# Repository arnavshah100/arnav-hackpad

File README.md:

# arnav-hackpad
<b>The arnav-hackpad is a mini-keyboard (or macropad) designed to act as an external number pad with navigation and mouse capabilities, too!</b>

## Inspiration
In my essential technology class at school, two of my favorite modules were coding and 3D printing. When I joined the [Stardance summer program](https://stardance.hackclub.com/) and started looking at the recommended projects, I saw <b>hackpad</b>, and saw it as a great way to combine my love for those two subjects.
## Features
- 2 EC11 Rotary Encoders with Switches
- 10 MX-Style Key Switches
- 3-Part Case (Top Mount style macropad)
- 2 Layers (When a layer is activated, all the keymaps change to that layer's configuration.)
## CAD Model
\
This is my assembled macropad. Click on it to interact with the assembled macropad in Autodesk Fusion's web version.\
_Note: The assembled macropad CAD model is just a quick visual. Some of the dimensions have been edited to optimize its usability. The links of the individual parts below have the correct dimensions._ 

There are 3 parts to the case: the top, the bottom, and the plate. The arnav-hackpad is top-mounted, meaning that the plate is attached to the top part. The design gives an ≈0.3mm printing tolerance. Also, there are 2 knobs I have put on top of the rotary encoders, called Hack Club Knurled Knobs. To personalize it, I added a cool design with my name on the plate, which you can see in the plate demo below!

[Click here to interact with the Plate.](https://a360.co/4g3hhWc)\
[Click here to interact with the Top part.](https://a360.co/4vbjJyh)\
[Click here to interact with the  Bottom part.](https://a360.co/4pMDXNC)\
[Click here to interact with the Hack Club Knurled Knob.](https://a360.co/4jsLTTg)
## PCB

This is my PCB's schematic design. Click on it to interact with the schematic in KiCanvas.

I used a PCF8574AT I/O expander because all of the pins would not fit on the microchip.

This is my PCB board. Click on it to interact with the PCB Board in KiCanvas.

I know it's very messy, but everything works out in the end!
## Firmware Overview
The macropad is coded using KMK firmware. Layer 0 is made to take the place of a number pad, and Layer 1 is made to take the place of a mouse and the arrow keys. For the rotary encoders, clockwise is up, and counterclockwise is down.
- On Layer 0 (Default),
    - The rotary encoder on the left changes volume, and its switch works as the mute key.
    - The rotary encoder on the right changes brightness, and its switch turns on layer 1.
    - The key switches are arranged in the same way as the numbers are in a number pad. 
- On Layer 1,
    - The rotary encoder on the left acts as a scroll wheel.
    - The rotary encoder on the right also acts as a scroll wheel, and its switch turns on layer 0.
    - The keyswitches are arranged as follows(refer to the PCB image):
        - SW1 is Left Click
        - SW2 is Up Arrow
        - SW3 is Right Click
        - SW4 is Left Arrow
        - SW5 is Down Arrow
        - SW6 is Right Arrow

_Note: All of the key arrangements can be customized by simply editing the code._
## How to make it
<b>If you need help for any part of this tutorial, Google can teach you!</b>
### Bill of Materials
To make this macropad, you will need the following:
- 10x Cherry MX Switches
- 10x 1N4148 DO-35 Diodes
- 10x DSA Keycaps
- 2x EC11 Rotary Encoder
- 2x Hack Club Knurled Knob (Replaceable with another knob for EC11 Rotary Encoder)
- 1x Seeed Studio XIAO RP2040
- 1x PCF8574AT
- 1x 0805 SMD Ceramic Capacitor - 100 nF, 50 V, ±10%
- 2x 0805 SMD Pull-Up Resistors - 4.7 kΩ
- 4x M3 x D5mm x L4mm Heatset Inserts
- 4x M2 x D4mm x L3mm Heatset Inserts
- 4x M3 x 16mm screws
- 4x M2 x 4mm screws
- 1x Case (3 printed parts)
- 1x USB-C cable
- 1x Soldering Iron
### Installing the Firmware
Download the [Production folder](Production/Firmware) onto your computer. [This guide](https://wiki.seeedstudio.com/XIAO-RP2040-with-CircuitPython/), from Seeed Studio, is great to help you import the firmware. Drag the files <b>out of the folder</b> and into the drive. Make sure every file and folder is in the drive when you're done. The code can still be edited after you put it in the drive!
### PCB
Use the [Gerbers.zip file](Production/Gerbers.zip) to print the PCB from whatever company you want. Make sure you choose the <b>2-layer</b> PCB option. When you solder the components together, make sure to refer to the [online PCB image](https://kicanvas.org/?repo=https%3A%2F%2Fgithub.com%2Farnavshah100%2Farnav-hackpad%2Fblob%2Fmain%2FPCB%2FKiCad%2520file.kicad_pcb) often. I recommend soldering the components in this order:
1. Diodes
2. Microcontroller and I/O Expander (XIAO RP2040 and PCF8574AT)
3. Ceramic Capacitors and Pull-Up Resistors
4. Rotary encoders
5. Mount keyswitches on plate in direction shown on PCB <b>FIRST</b>, and <b>THEN</b> solder them on.
### 3D Printing
Use the [Plate.step file](Production/CAD%20files/Plate.step), [Top.step file](Production/CAD%20files/Top.step), [Bottom.step file](Production/CAD%20files/Bottom.step), and [Hack Club Knurled Knob.step file in case you are using it](Production/CAD%20files/Hack%20Club%20Knurled%20Knob.step). If you are printing it yourself, I suggest using google to figure out how to print on your specific 3D printer. Otherwise, just give the files above to whoever is printing it. Make sure you use either PLA, ABS, PETG, or Nylon, because certain plastics don't work with heatset inserts.
### Assembly

Finally, it's time to do the assembly! Put the M3 x D5mm x L4mm heatset inserts on the outer holes of the top part, and put the M2 x D4mm x L3mm heatset inserts on the inner holes of the top part. You can use [this image](Assets/ScrewImage.png) to help you.

Next, <b><i><u>carefully</u></i></b> solder the keyswitches onto the PCB.

For the last step, use the M2x4mm screws to screw the plate onto the top part's M2 heatset insert. The top part of the screw should be touching the plate. I recommend plugging in the PCB into your device and trying using the macropad to check that it works. If your device doesn't register any of the keypresses, reread all the steps in [the guide](https://github.com/arnavshah100/arnav-hackpad/#how-to-make-it). Use the M3x16mm screws to screw the bottom part onto the top part's M3 heatset insert. The top part of the screw should be touching the bottom part. The labeled image showing where the screws should be is [here](Assets/Assembly.png).

Now, put the knobs on the rotary encoders, and you're DONE! 

<b><u>CELEBRATE!</u></b>
## Final Product
After over 3 months of dedication, I have built the arnav-hackpad.\

This is the image of the hackpad.\
[arnav-hackpad video](https://github.com/arnavshah100/arnav-hackpad/raw/refs/heads/main/Assets/Video.mov)\
This is a video demoing the hackpad. Click on it to watch it!
## License
The code is under an MIT License. For more info, see [LICENSE](LICENSE).
## Credits
- Huge thanks to [@ashah80](https://github.com/ashah80) (my brother!), who helped me in every step of the way, even though he has never made anything hardware-related.
- I was motivated by the [Stardance summer program](https://stardance.hackclub.com/), which both inspired and incentivized me to make this project. I had never even considered making anything related to hardware before Stardance provided me with a great platform to do so.
- The people in the [hackpad slack page](https://hackclub.enterprise.slack.com/archives/C07LESGH0B0) from Hack Club helped answer all my questions.
- I used [Claude](claude.ai) to help me learn how to code in KMK, specifically for the PCF8574AT scanner. It also gave me next steps for what to do when my hackpad didn't work. [Gemini](gemini.google.com) helped me with my general questions for how to use a software.
### Resources I used
- I used [Hack Club's KiCad care package](https://github.com/hackclub/hackpad/releases/tag/v0.1-bugfix) for some of my symbols and footprints in my PCB.
- I used [KiCad's rotary encoder footprint](https://kicad.github.io/footprints/Rotary_Encoder) for my, well, rotary encoder!
- I used [Hack Club's rotary encoder and knurled knob CAD file](https://github.com/hackclub/hackpad/tree/clean/extras/CAD%20models) in my [assembled hackpad file](CAD/arnav-hackpad.step).
- I used some of the [KMK's CircuitPython libraries](https://github.com/KMKfw/kmk_firmware), a key part of my code.
- I used [CircuitPython's code language interpreter](https://circuitpython.org/board/seeeduino_xiao_rp2040/) as the main software.

<b>Thank you for <i>reading me</i>!</b>

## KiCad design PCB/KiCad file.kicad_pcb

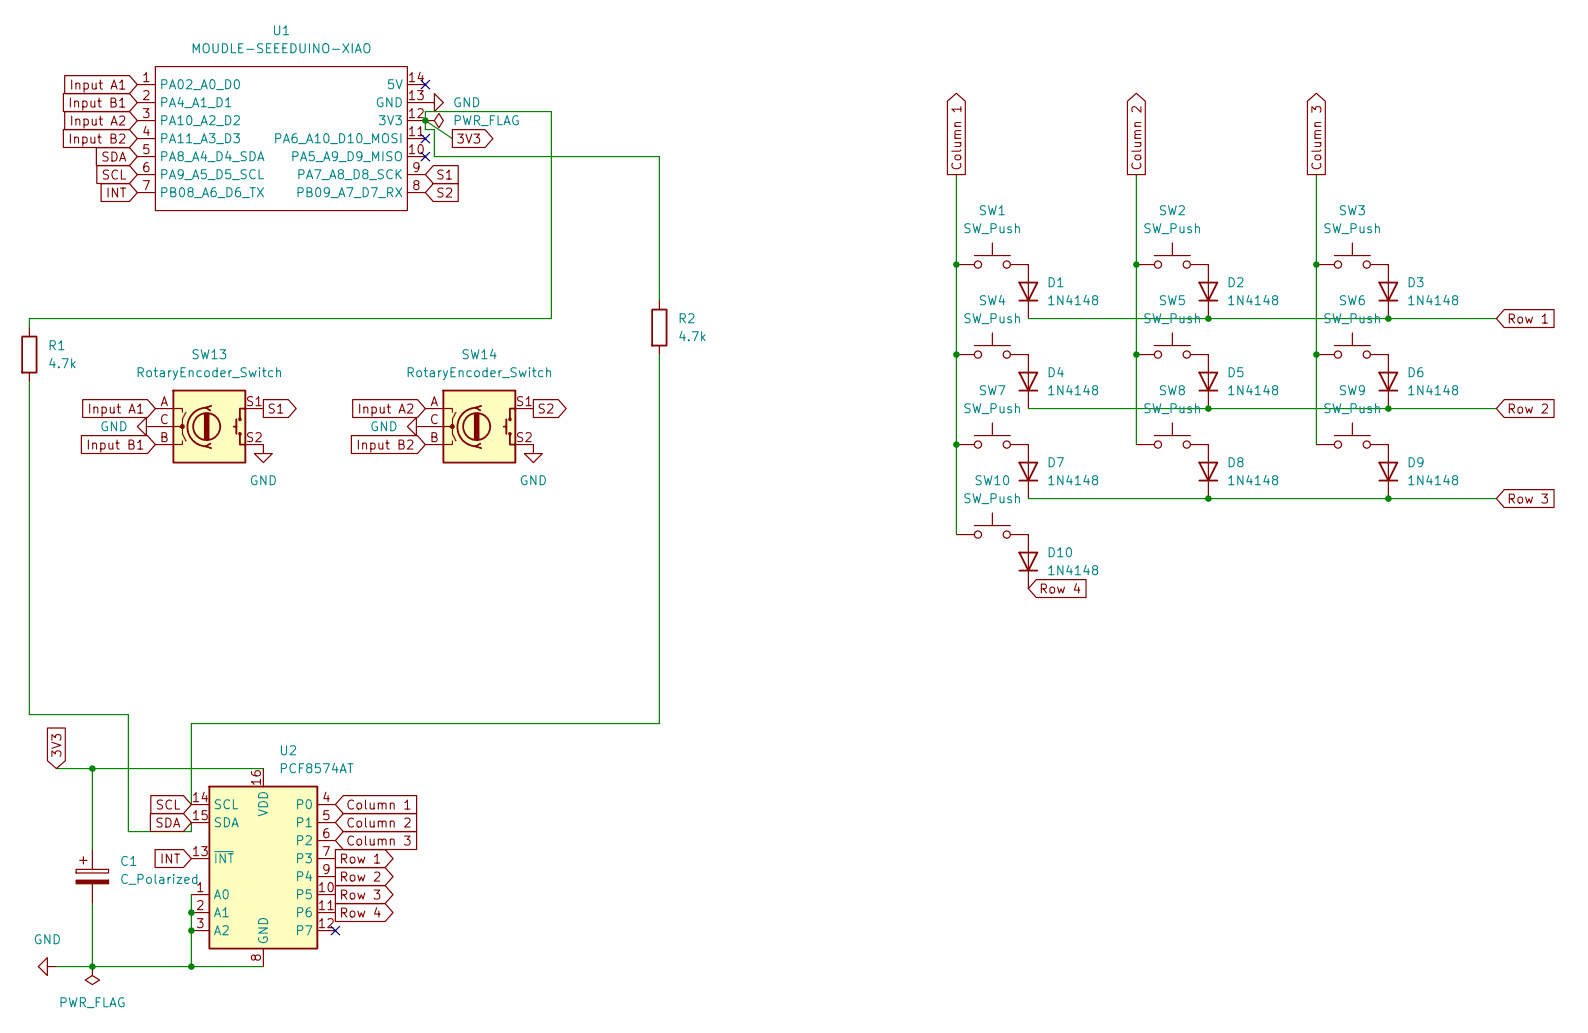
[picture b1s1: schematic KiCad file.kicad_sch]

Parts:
C1: C_Polarized; C_0805_2012Metric; LCSC Part # C49678
D1, D2, D3, D4, D5, D6, D7, D8, D9, D10: 1N4148; D_DO-35_SOD27_P7.62mm_Horizontal; LCSC Part # C85057
R1, R2: 4.7k; R_0805_2012Metric
SW1, SW2, SW3, SW4, SW5, SW6, SW7, SW8, SW9, SW10: SW_Push; SW_Cherry_MX_1.00u_PCB; JLCPCB Part # C9900177322
SW13, SW14: RotaryEncoder_Switch; RotaryEncoder_Alps_EC11E-Switch_Vertical_H20mm
U1: MOUDLE-SEEEDUINO-XIAO; XIAO-Generic-Hybrid-14P-2.54-21X17.8MM
U2: PCF8574AT; SOIC-16W_7.5x10.3mm_P1.27mm; LCSC Part # C86832

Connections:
3V3: C1.1, R1.1, R2.1, U1.12 (3V3), U2.16 (VDD)
Column 1: SW1.1, SW4.1, SW7.1, SW10.1, U2.4 (P0)
Column 2: SW2.1, SW5.1, SW8.1, U2.5 (P1)
Column 3: SW3.1, SW6.1, SW9.1, U2.6 (P2)
GND: C1.2, SW13.C, SW13.S2, SW14.C, SW14.S2, U1.13 (GND), U2.1 (A0), U2.2 (A1), U2.3 (A2), U2.8 (GND)
INT: U1.7 (PB08_A6_D6_TX), U2.13 (~INT)
Input A1: SW13.A, U1.1 (PA02_A0_D0)
Input A2: SW14.A, U1.3 (PA10_A2_D2)
Input B1: SW13.B, U1.2 (PA4_A1_D1)
Input B2: SW14.B, U1.4 (PA11_A3_D3)
unnamed: D1.2 (A), SW1.2
unnamed: D2.2 (A), SW2.2
unnamed: D3.2 (A), SW3.2
unnamed: D4.2 (A), SW4.2
unnamed: D5.2 (A), SW5.2
unnamed: D6.2 (A), SW6.2
unnamed: D7.2 (A), SW7.2
unnamed: D8.2 (A), SW8.2
unnamed: D9.2 (A), SW9.2
unnamed: D10.2 (A), SW10.2
Row 1: D1.1 (K), D2.1 (K), D3.1 (K), U2.7 (P3)
Row 2: D4.1 (K), D5.1 (K), D6.1 (K), U2.9 (P4)
Row 3: D7.1 (K), D8.1 (K), D9.1 (K), U2.10 (P5)
Row 4: D10.1 (K), U2.11 (P6)
S1: SW13.S1, U1.9 (PA7_A8_D8_SCK)
S2: SW14.S1, U1.8 (PB09_A7_D7_RX)
SCL: R2.2, U1.6 (PA9_A5_D5_SCL), U2.14 (SCL)
SDA: R1.2, U1.5 (PA8_A4_D4_SDA), U2.15 (SDA)

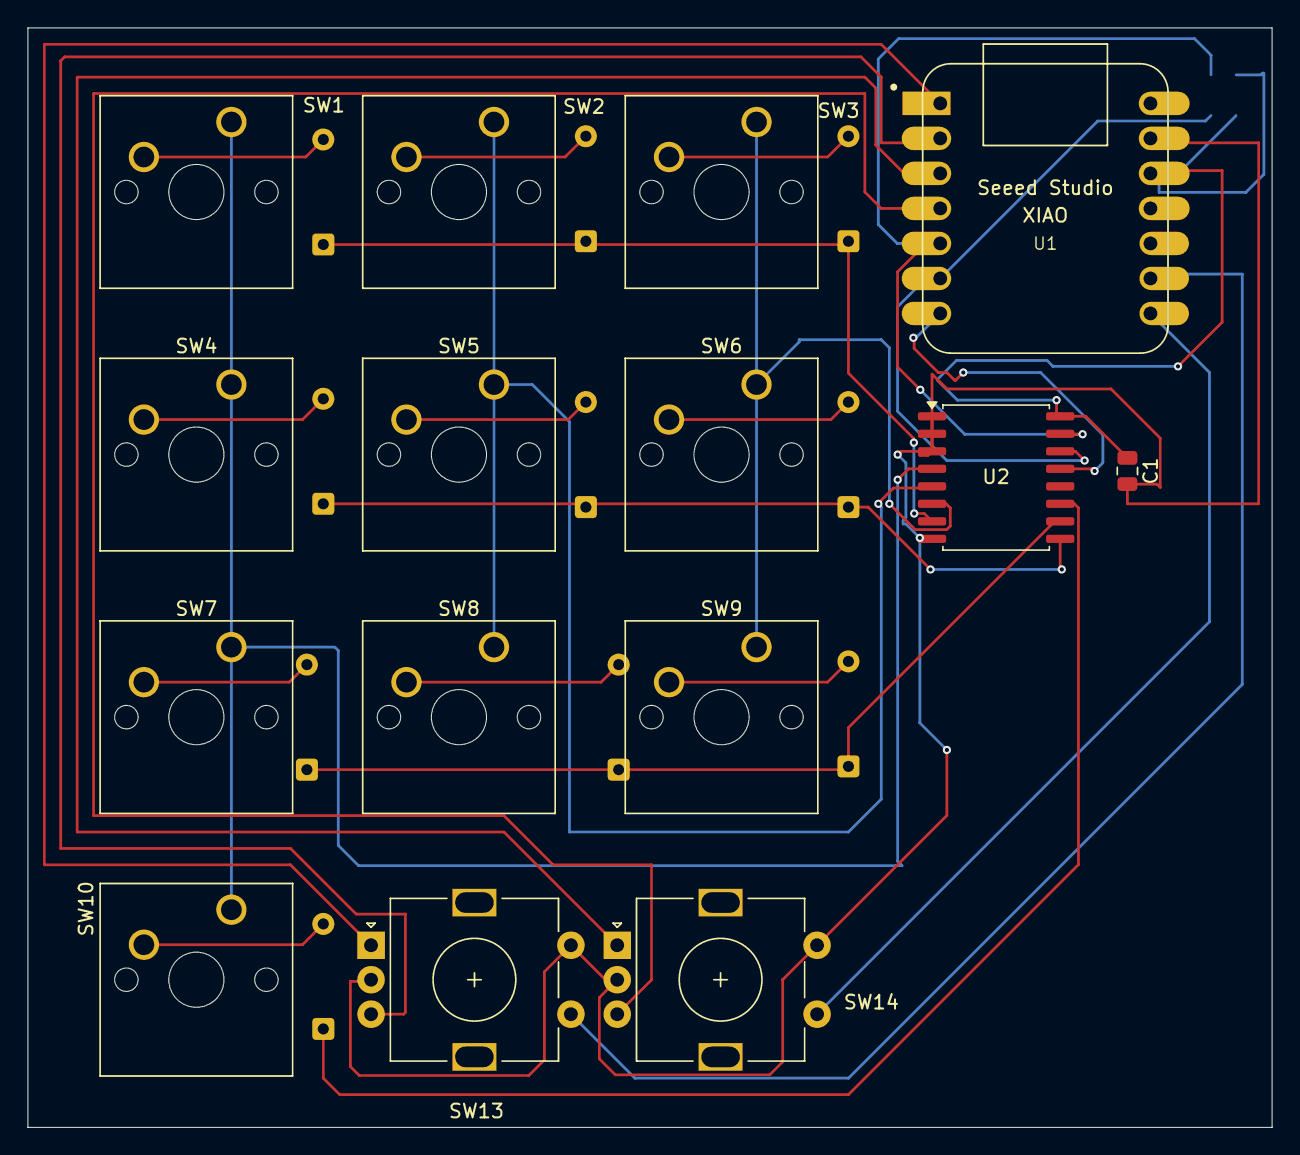
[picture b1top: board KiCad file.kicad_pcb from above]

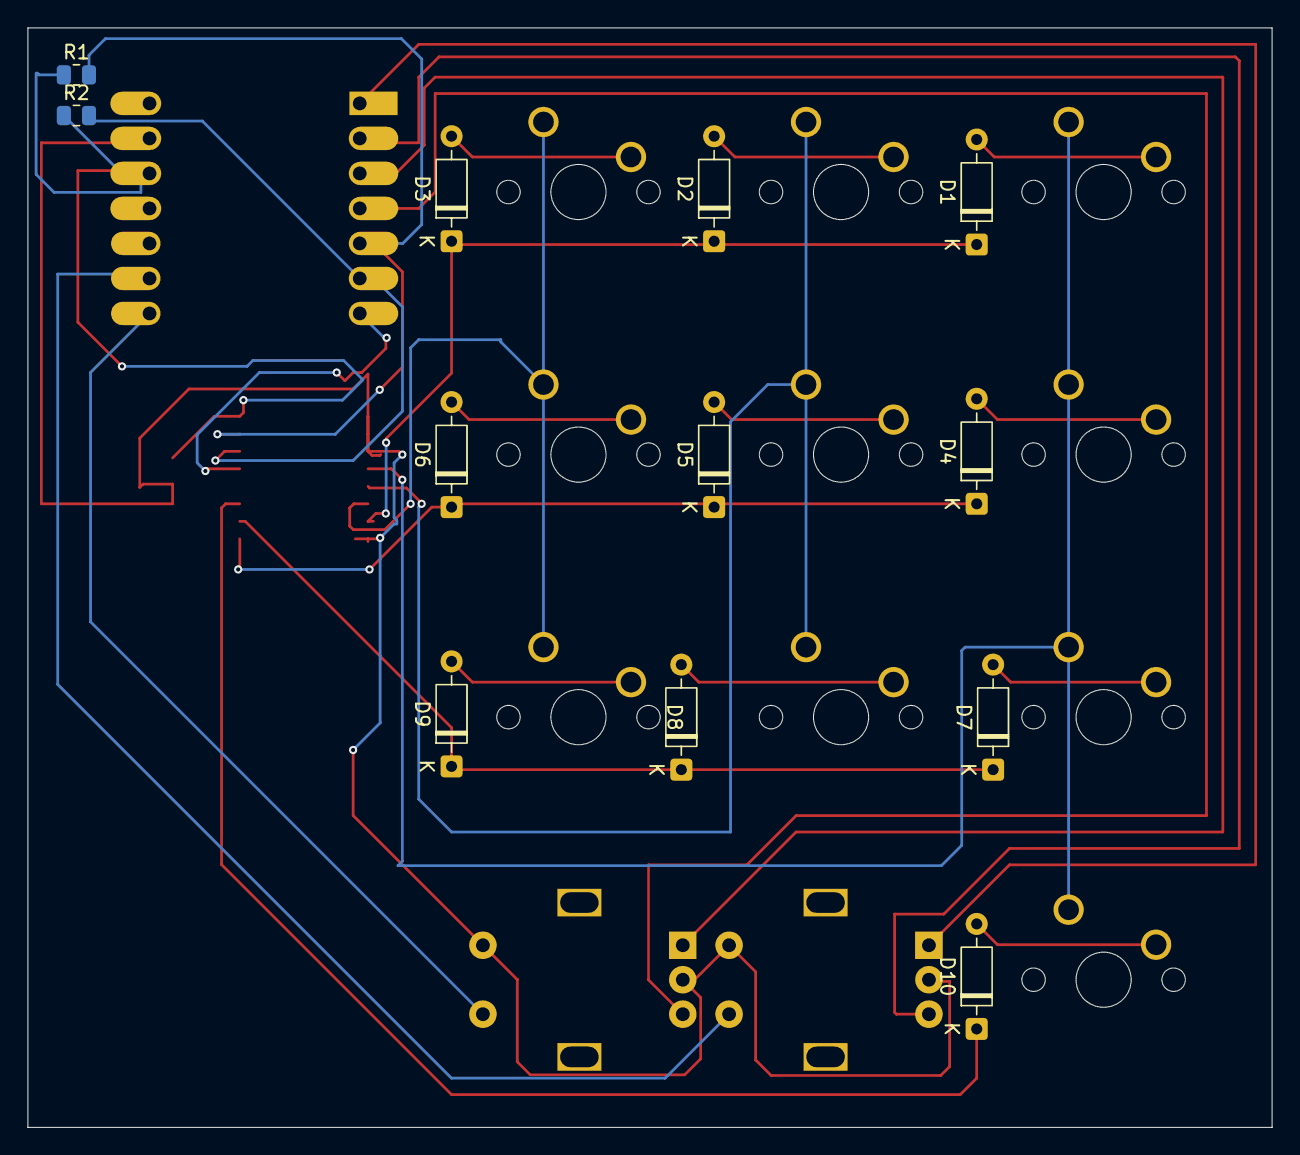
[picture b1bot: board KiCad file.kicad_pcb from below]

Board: 2 copper layers, 90.3 x 79.8 mm, 27 parts (12 on the bottom side), 28 nets.
